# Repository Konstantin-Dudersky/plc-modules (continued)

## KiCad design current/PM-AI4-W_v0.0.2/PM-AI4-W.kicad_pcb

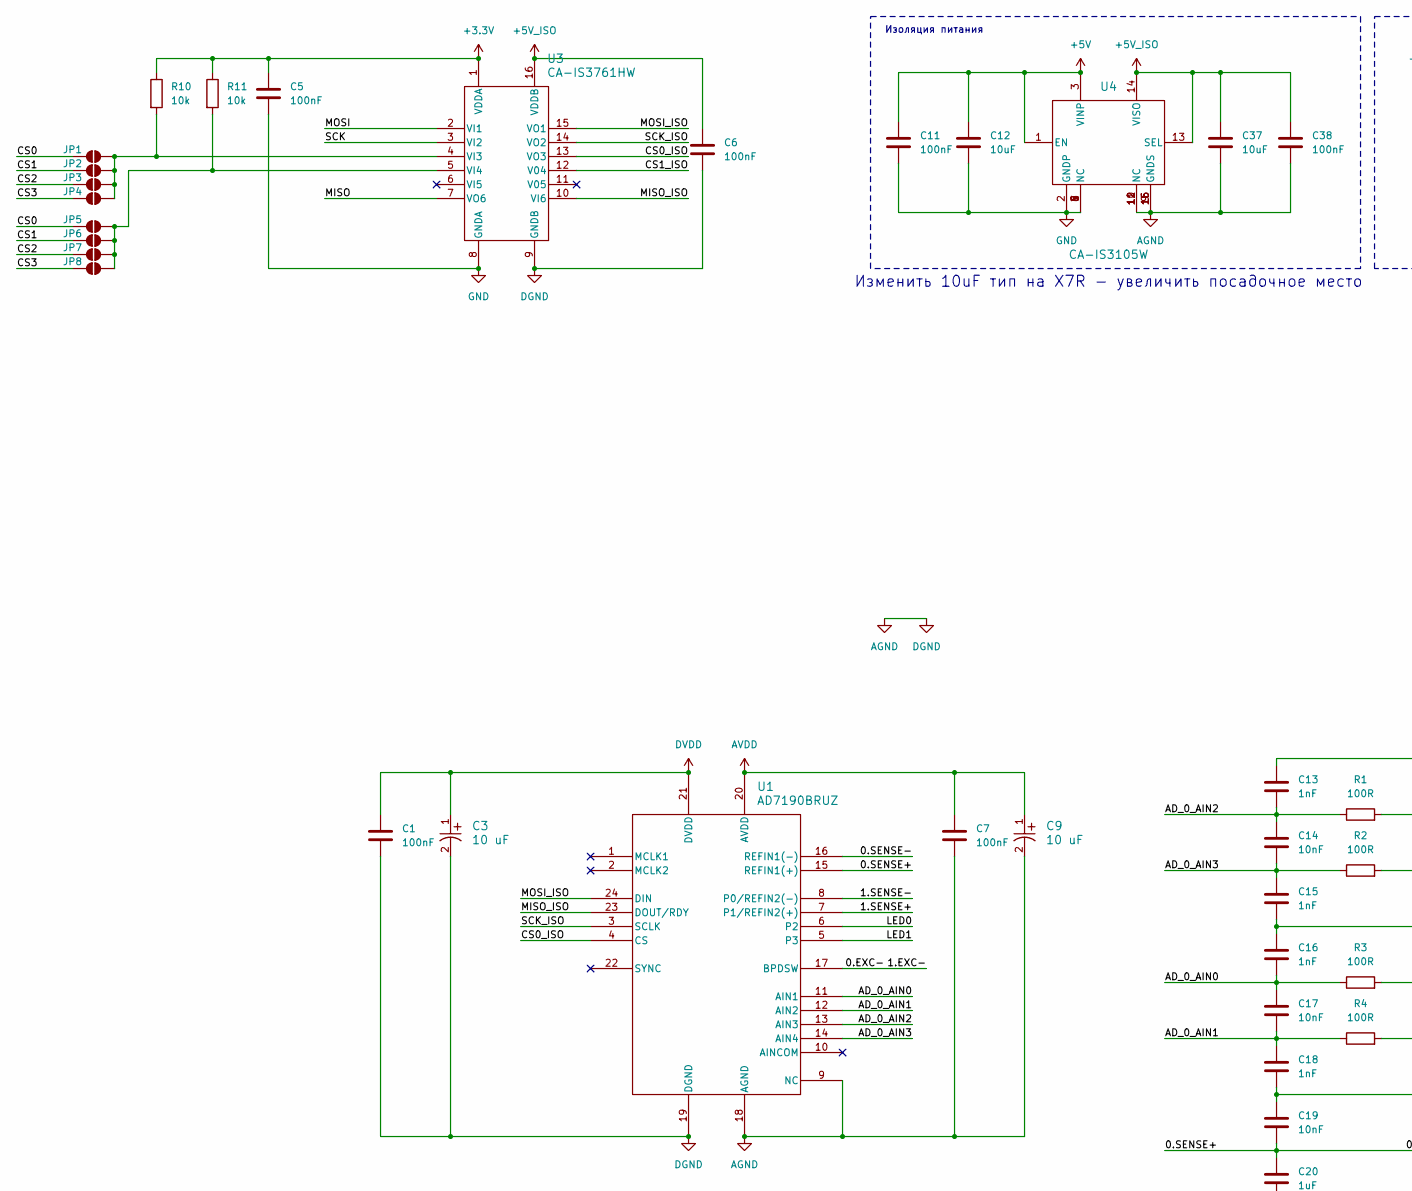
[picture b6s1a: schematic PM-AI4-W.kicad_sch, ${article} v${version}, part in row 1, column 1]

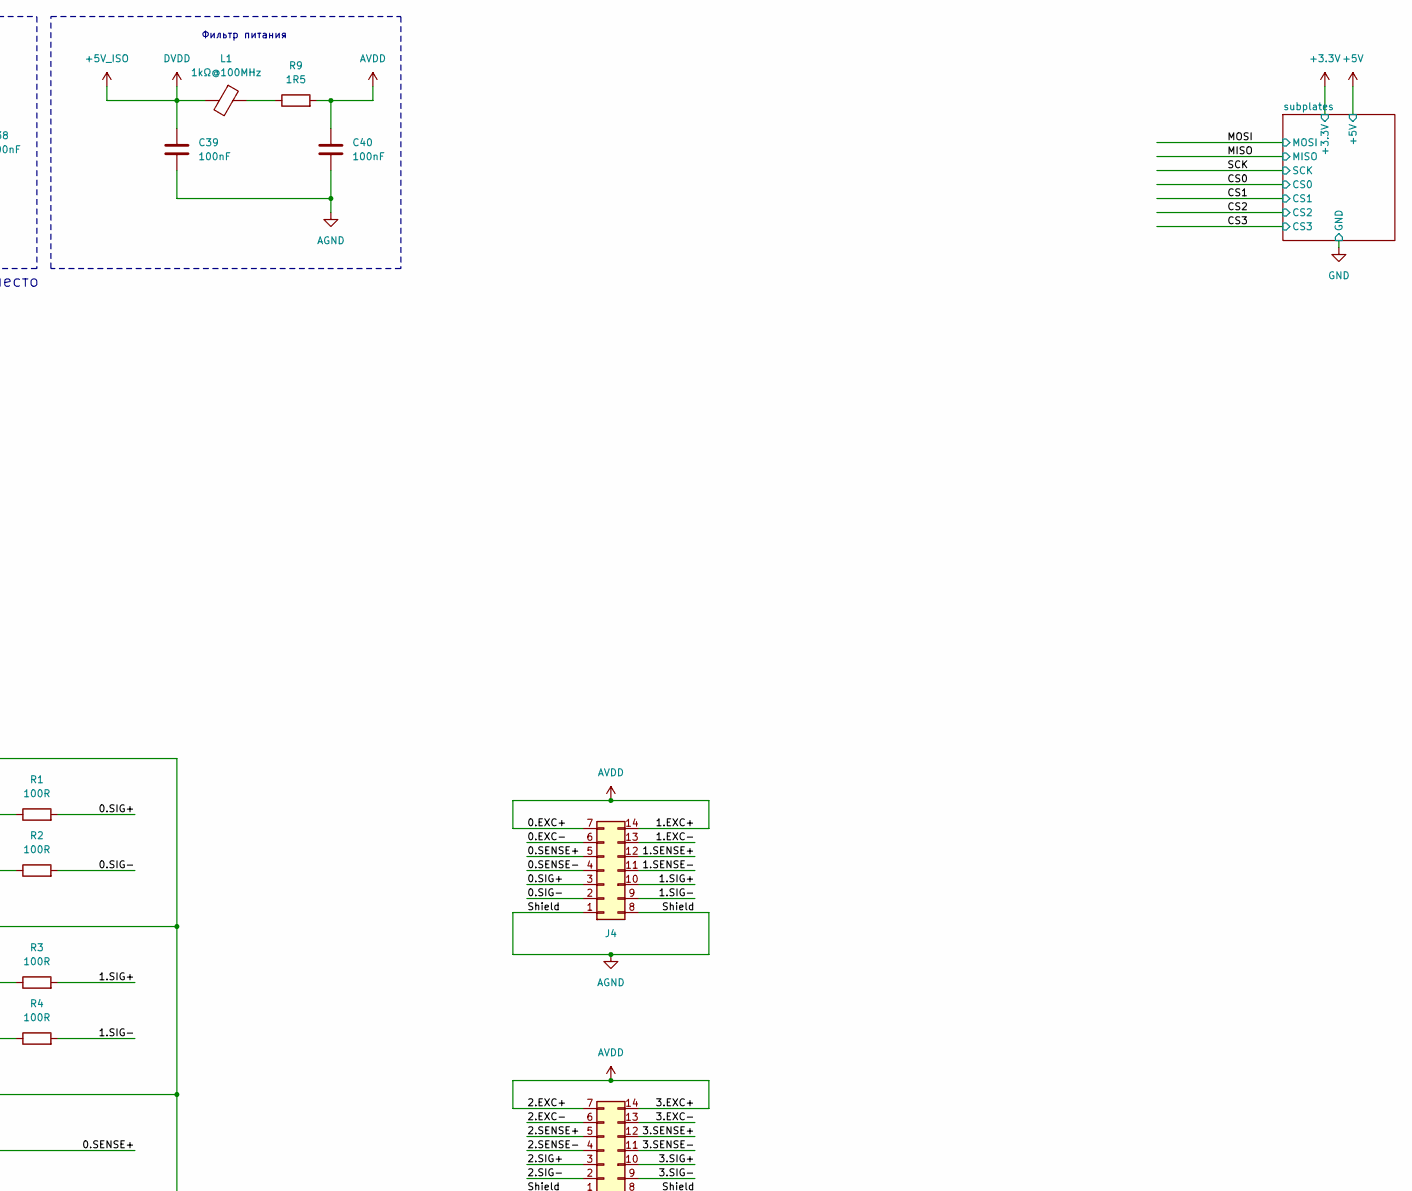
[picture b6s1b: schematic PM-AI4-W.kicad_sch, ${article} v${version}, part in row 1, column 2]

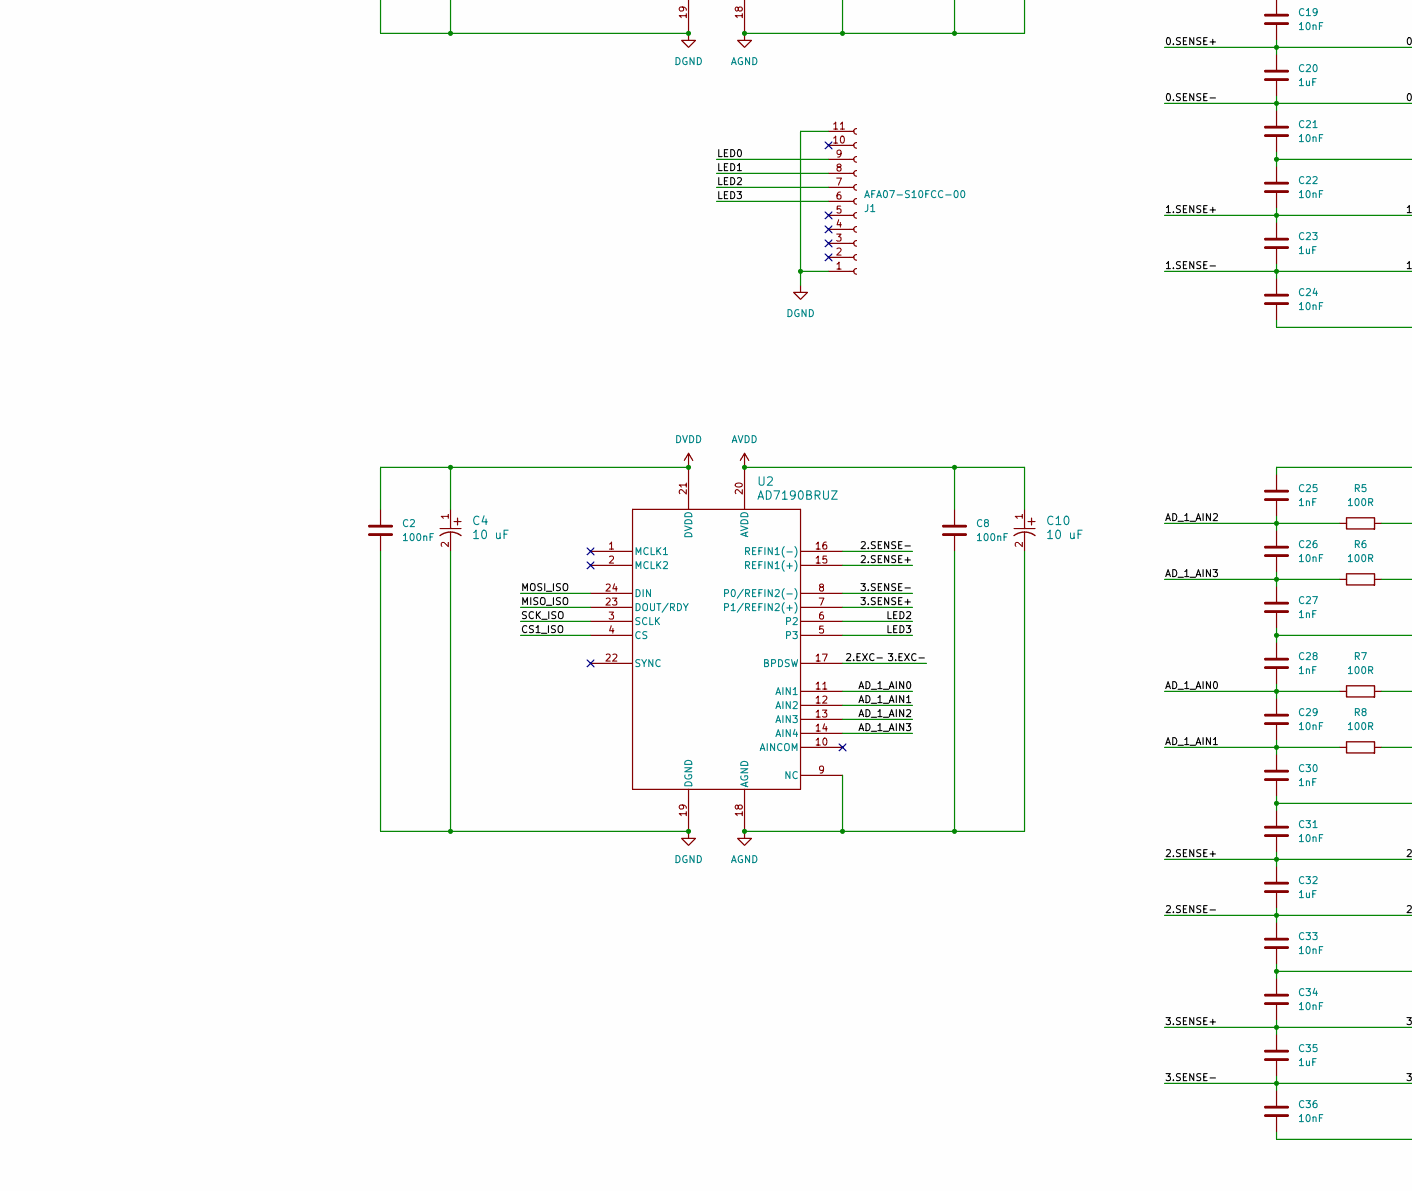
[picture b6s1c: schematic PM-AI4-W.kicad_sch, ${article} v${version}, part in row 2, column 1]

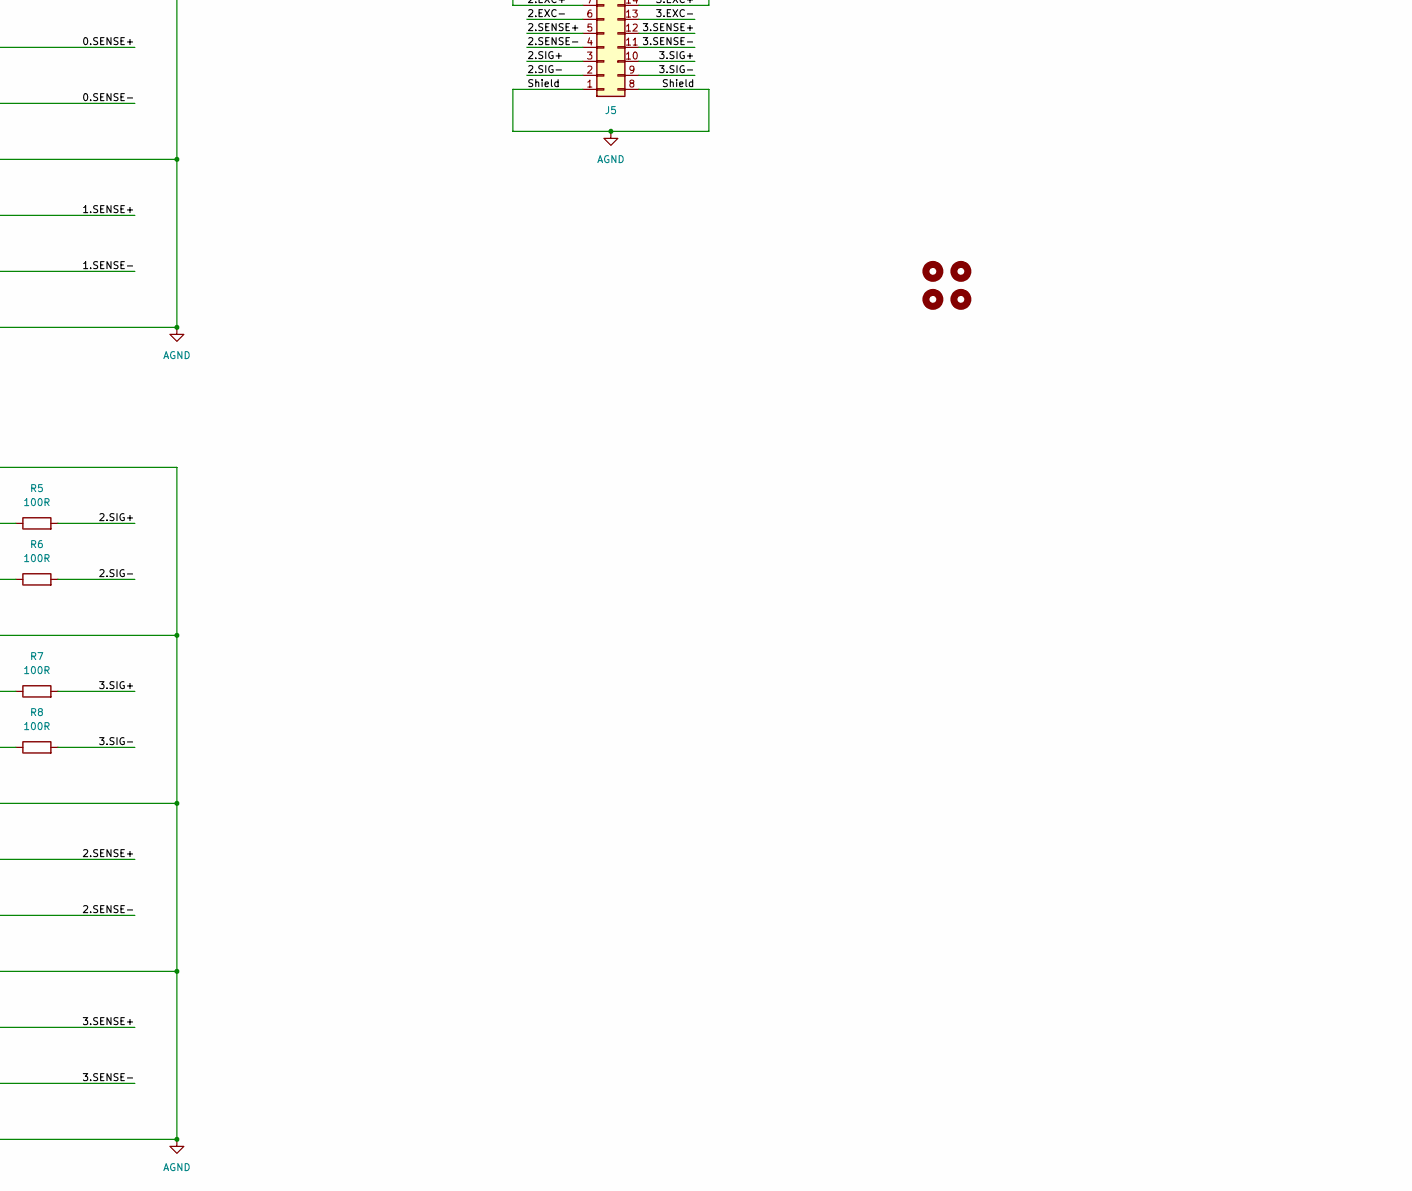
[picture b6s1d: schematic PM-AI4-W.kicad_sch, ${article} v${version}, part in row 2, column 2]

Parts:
C1, C2, C5, C6, C7, C8, C11, C38, C39, C40: 100nF; C_0603_1608Metric; part_ipn C_100nF_16V_0603_MLCC-X7R
C3, C4, C9, C10: 10 uF; TAJA_AVX-M; part_ipn TAJA106M016RNJ
C12, C37: 10uF; C_0603_1608Metric; part_ipn C_10uF_16V_0603_MLCC-X5R
C13, C15, C16, C18, C25, C27, C28, C30: 1nF; C_0603_1608Metric; part_ipn C_1nF_16V_0603_MLCC-X7R
C14, C17, C19, C21, C22, C24, C26, C29, C31, C33, C34, C36: 10nF; C_0603_1608Metric; part_ipn C_10nF_16V_0603_MLCC-X7R
C20, C23, C32, C35: 1uF; C_0603_1608Metric; part_ipn C_1uF_16V_0603_MLCC-X7R
H1, H2, H3, H4: MountingHole_M3
J1: AFA07-S10FCC-00; CONN10_AFA07-S10_JUS; part_ipn AFA07-S10FCC-00
J4, J5: 15EDGRHC-THR-3.5-14P; part_ipn 15EDGRHC-THR-3.5-14P
JP1, JP2, JP3, JP4, JP5, JP6, JP7, JP8: SolderJumper_2_Open; SolderJumper-2_P1.3mm_Open_RoundedPad1.0x1.5mm
L1: 1kΩ@100MHz; L_1206_3216Metric_Pad1.42x1.75mm_HandSolder; part_ipn FB_300mΩ_1kΩ@100MHz_1206
R1, R2, R3, R4, R5, R6, R7, R8: 100R; R_0603_1608Metric; part_ipn R_100R_0603_1%
R9: 1R5; R_0603_1608Metric; part_ipn R_1R5_0603_1%
R10, R11: 10k; R_0603_1608Metric; part_ipn R_10k_0603_1%
U1, U2: AD7190BRUZ; RU_24_ADI-M; part_ipn AD7190
U3: CA-IS3761HW; SOIC16-WBW_CLG-M; part_ipn CA-IS3761HW
U4: CA-IS3105W; SOIC16-WBW_CLG-M; part_ipn CA-IS3105W

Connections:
+3.3V: C5.1, R10.1, R11.1, U3.1 (VDDA); also elsewhere on the board
+5V: C11.1, C12.1, U4.1 (EN), U4.3 (VINP); also elsewhere on the board
+5V_ISO: C1.1, C2.1, C3.1, C4.1, C6.1, C37.1, C38.1, C39.1, L1.2, U1.21 (DVDD), U2.21 (DVDD), U3.16 (VDDB), U4.13 (SEL), U4.14 (VISO)
/0.EXC-: J4.6 (Pin_9), J4.13 (Pin_10), U1.17 (BPDSW)
/0.SENSE+: C19.2, C20.1, J4.5 (Pin_9), U1.15 (REFIN1(+))
/0.SENSE-: C20.2, C21.1, J4.4, U1.16 (REFIN1(-))
/0.SIG+: J4.3, R1.2
/0.SIG-: J4.2 (Pin_3), R2.2
/1.SENSE+: C22.2, C23.1, J4.12 (Pin_10), U1.7 (P1/REFIN2(+))
/1.SENSE-: C23.2, C24.1, J4.11 (Pin_8), U1.8 (P0/REFIN2(-))
/1.SIG+: J4.10 (Pin_6), R3.2
/1.SIG-: J4.9 (Pin_4), R4.2
/2.EXC-: J5.6 (Pin_9), J5.13 (Pin_10), U2.17 (BPDSW)
/2.SENSE+: C31.2, C32.1, J5.5 (Pin_9), U2.15 (REFIN1(+))
/2.SENSE-: C32.2, C33.1, J5.4, U2.16 (REFIN1(-))
/2.SIG+: J5.3, R5.2
/2.SIG-: J5.2 (Pin_3), R6.2
/3.SENSE+: C34.2, C35.1, J5.12 (Pin_10), U2.7 (P1/REFIN2(+))
/3.SENSE-: C35.2, C36.1, J5.11 (Pin_8), U2.8 (P0/REFIN2(-))
/3.SIG+: J5.10 (Pin_6), R7.2
/3.SIG-: J5.9 (Pin_4), R8.2
/AD_0_AIN0: C16.2, C17.1, R3.1, U1.11 (AIN1)
/AD_0_AIN1: C17.2, C18.1, R4.1, U1.12 (AIN2)
/AD_0_AIN2: C13.2, C14.1, R1.1, U1.13 (AIN3)
/AD_0_AIN3: C14.2, C15.1, R2.1, U1.14 (AIN4)
/AD_1_AIN0: C28.2, C29.1, R7.1, U2.11 (AIN1)
/AD_1_AIN1: C29.2, C30.1, R8.1, U2.12 (AIN2)
/AD_1_AIN2: C25.2, C26.1, R5.1, U2.13 (AIN3)
/AD_1_AIN3: C26.2, C27.1, R6.1, U2.14 (AIN4)
/CS0: JP1.1 (A), JP5.1 (A); also elsewhere on the board
/CS0_ISO: U1.4 (CS), U3.13 (VO3)
/CS1: JP2.1 (A), JP6.1 (A); also elsewhere on the board
/CS1_ISO: U2.4 (CS), U3.12 (V04)
/CS2: JP3.1 (A), JP7.1 (A); also elsewhere on the board
/CS3: JP4.1 (A), JP8.1 (A); also elsewhere on the board
/LED0: J1.9, U1.6 (P2)
/LED1: J1.8, U1.5 (P3)
/LED2: J1.7, U2.6 (P2)
/LED3: J1.6, U2.5 (P3)
/MISO: U3.7 (VO6); also elsewhere on the board
/MISO_ISO: U1.23 (DOUT/RDY), U2.23 (DOUT/RDY), U3.10 (VI6)
/MOSI: U3.2 (VI1); also elsewhere on the board
/MOSI_ISO: U1.24 (DIN), U2.24 (DIN), U3.15 (VO1)
/SCK: U3.3 (VI2); also elsewhere on the board
/SCK_ISO: U1.3 (SCLK), U2.3 (SCLK), U3.14 (VO2)
AGND: C1.2, C2.2, C3.2, C4.2, C6.2, C7.2, C8.2, C9.2, C10.2, C13.1, C15.2, C16.1, C18.2, C19.1, C21.2, C22.1, C24.2, C25.1, C27.2, C28.1, C30.2, C31.1, C33.2, C34.1, C36.2, C37.2, C38.2, C39.2, C40.2, J1.1, J1.11, J4.1, J4.8 (Pin_2), J5.1, J5.8 (Pin_2), U1.9 (NC), U1.18 (AGND), U1.19 (DGND), U2.9 (NC), U2.18 (AGND), U2.19 (DGND), U3.9 (GNDB), U4.9 (GNDS), U4.10 (NC), U4.11 (NC), U4.12 (NC), U4.15 (GNDS), U4.16 (GNDS)
AVDD: C7.1, C8.1, C9.1, C10.1, C40.1, J4.7 (Pin_9), J4.14 (Pin_10), J5.7 (Pin_9), J5.14 (Pin_10), R9.2, U1.20 (AVDD), U2.20 (AVDD)
GND: C5.2, C11.2, C12.2, U3.8 (GNDA), U4.2 (GNDP), U4.4 (NC), U4.5 (NC), U4.6 (NC), U4.7 (NC), U4.8 (NC); also elsewhere on the board
unnamed: JP1.2 (B), JP2.2 (B), JP3.2 (B), JP4.2 (B), R10.2, U3.4 (VI3)
unnamed: JP5.2 (B), JP6.2 (B), JP7.2 (B), JP8.2 (B), R11.2, U3.5 (VI4)
unnamed: L1.1, R9.1

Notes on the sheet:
Изменить 10uF тип на X7R - увеличить посадочное место
Фильтр питания
Изоляция питания

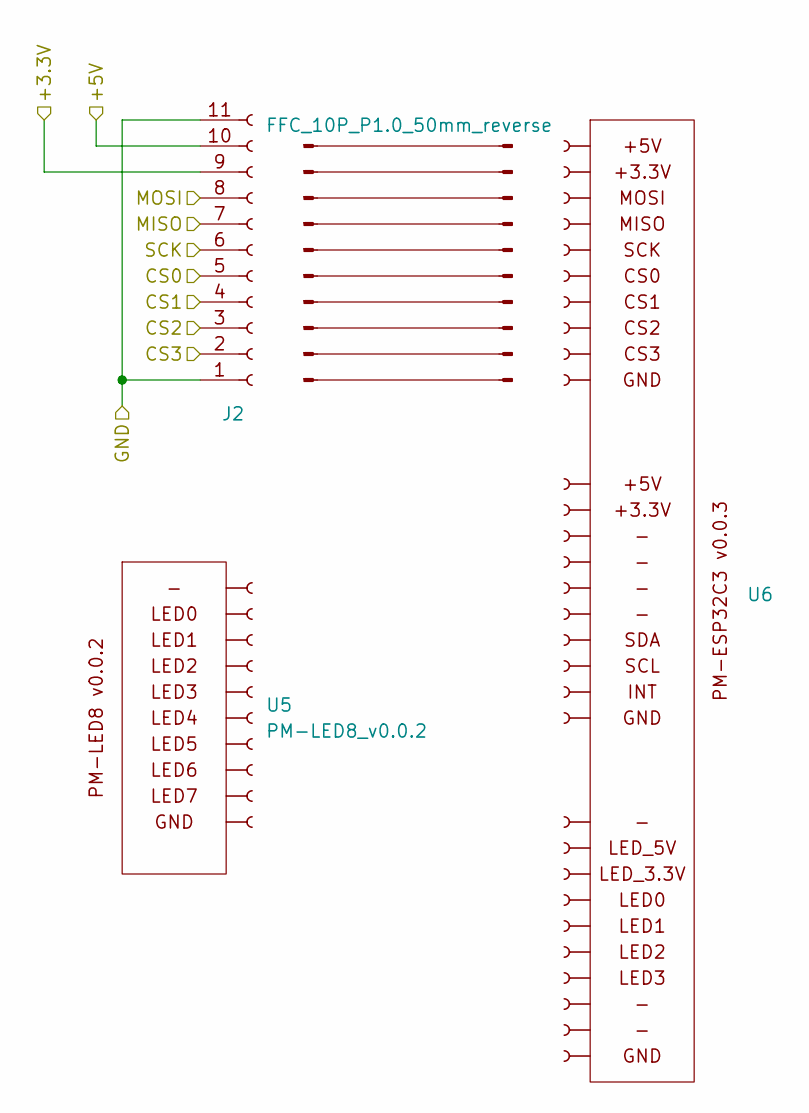
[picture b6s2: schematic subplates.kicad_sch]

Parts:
J2: AFA07-S10FCC-00; CONN10_AFA07-S10_JUS; part_ipn AFA07-S10FCC-00
J3: FFC_10P_P1.0_50mm_reverse; part_ipn FFC_10P_P1.0_50mm_reverse
U5: PM-LED8_v0.0.2; PM-LED_v0.0.2; part_ipn PM-LED8_v0.0.2
U6: PM-ESP32C3_v0.0.4; part_ipn PM-ESP32C3_v0.0.4

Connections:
+3.3V: J2.9; also elsewhere on the board
+5V: J2.10; also elsewhere on the board
/CS0: J2.5; also elsewhere on the board
/CS1: J2.4; also elsewhere on the board
/CS2: J2.3; also elsewhere on the board
/CS3: J2.2; also elsewhere on the board
/MISO: J2.7; also elsewhere on the board
/MOSI: J2.8; also elsewhere on the board
/SCK: J2.6; also elsewhere on the board
GND: J2.1, J2.11; also elsewhere on the board

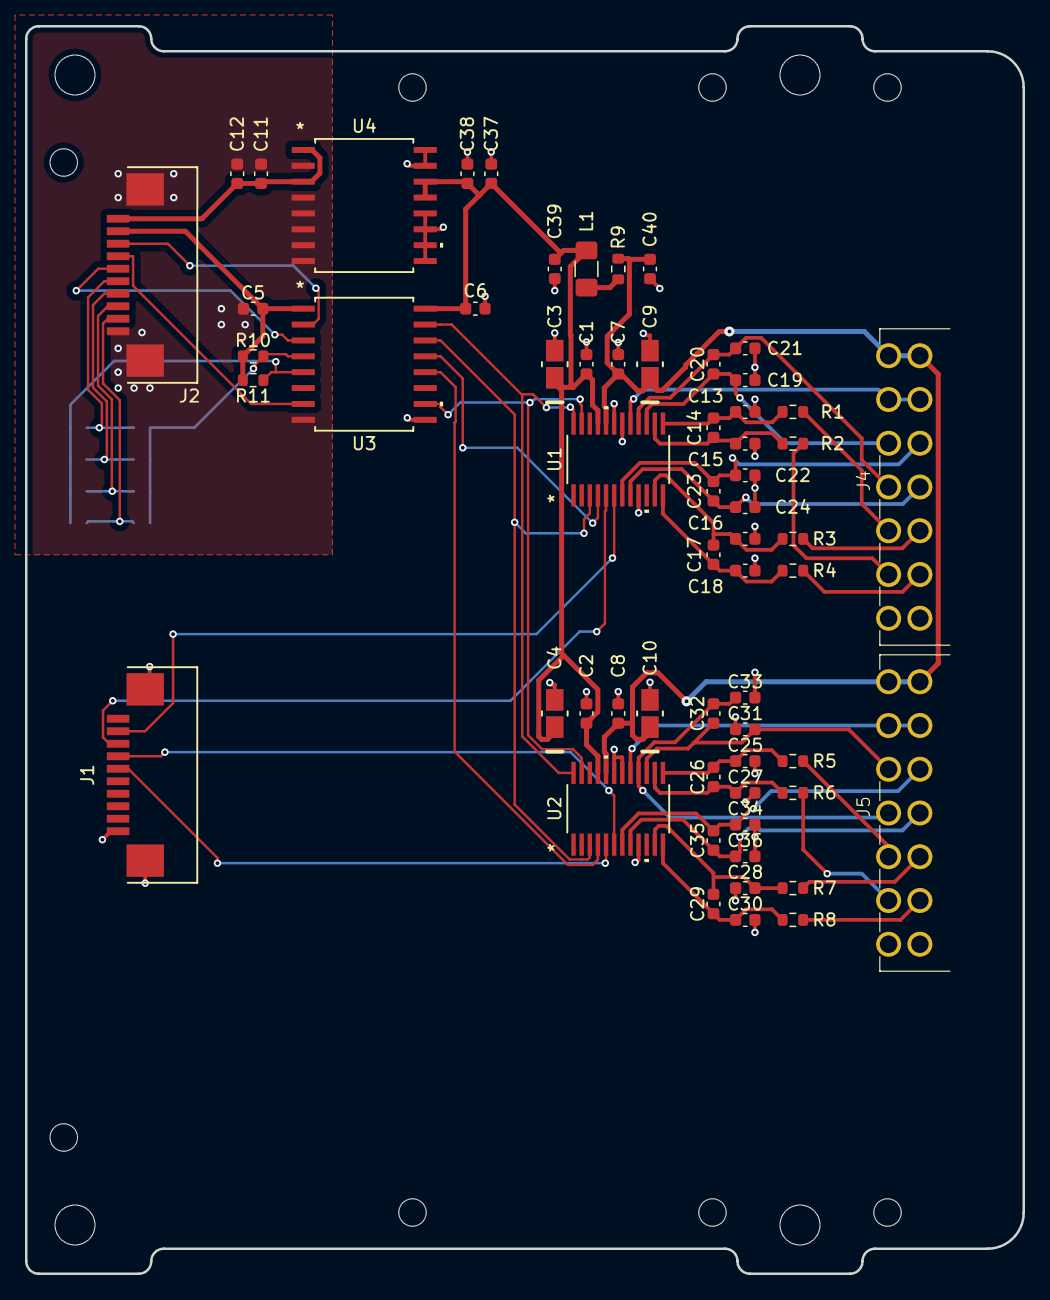
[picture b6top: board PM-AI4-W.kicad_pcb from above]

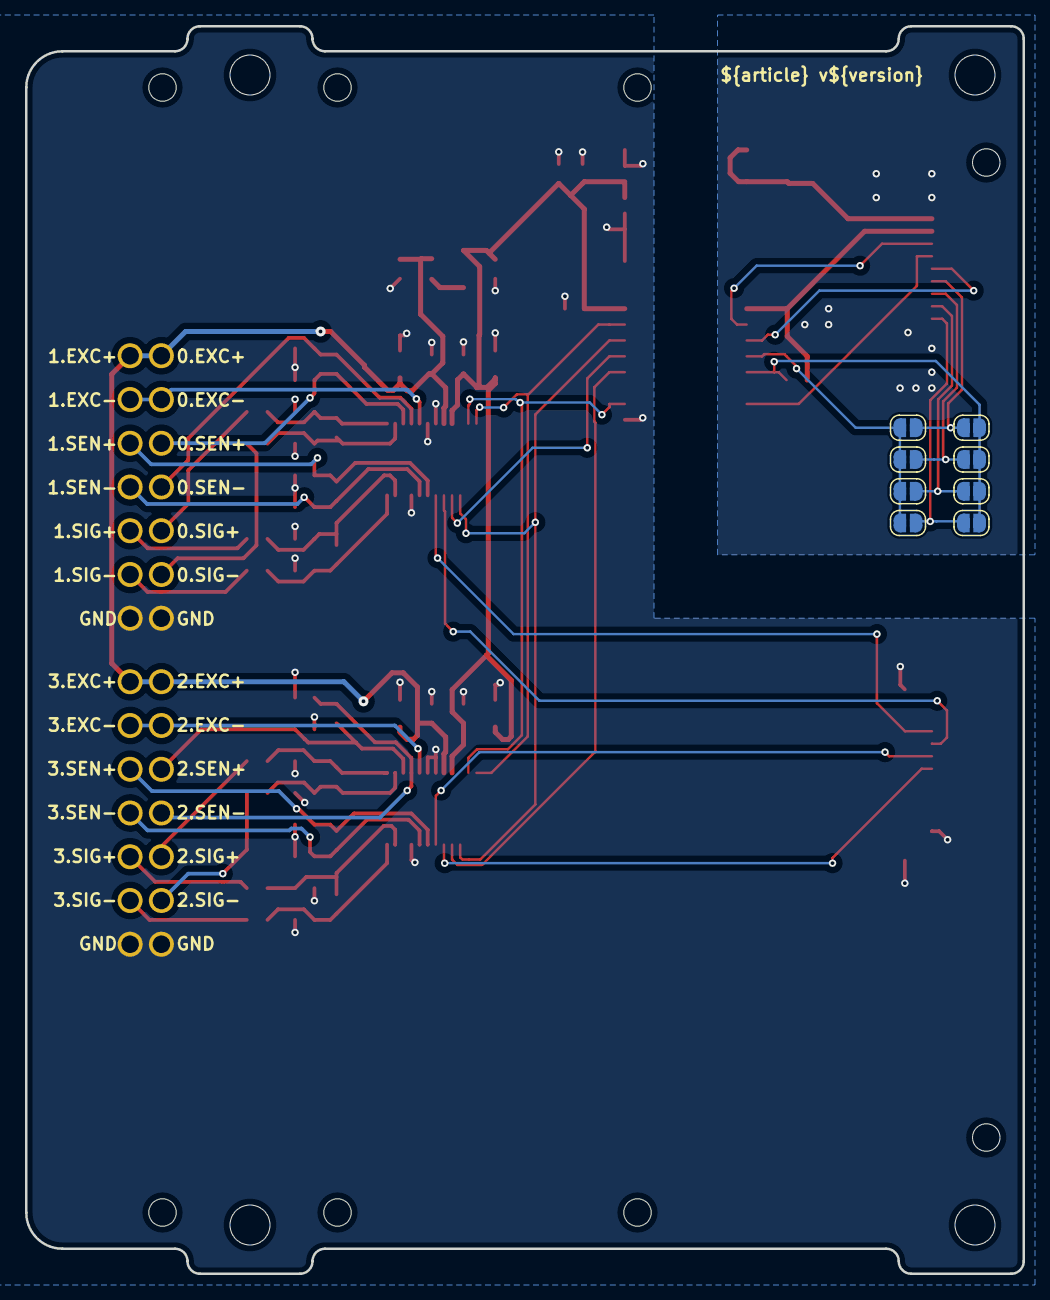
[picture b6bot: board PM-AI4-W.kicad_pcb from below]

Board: 2 copper layers, 79.8 x 99.8 mm, 74 parts (8 on the bottom side), 51 nets.

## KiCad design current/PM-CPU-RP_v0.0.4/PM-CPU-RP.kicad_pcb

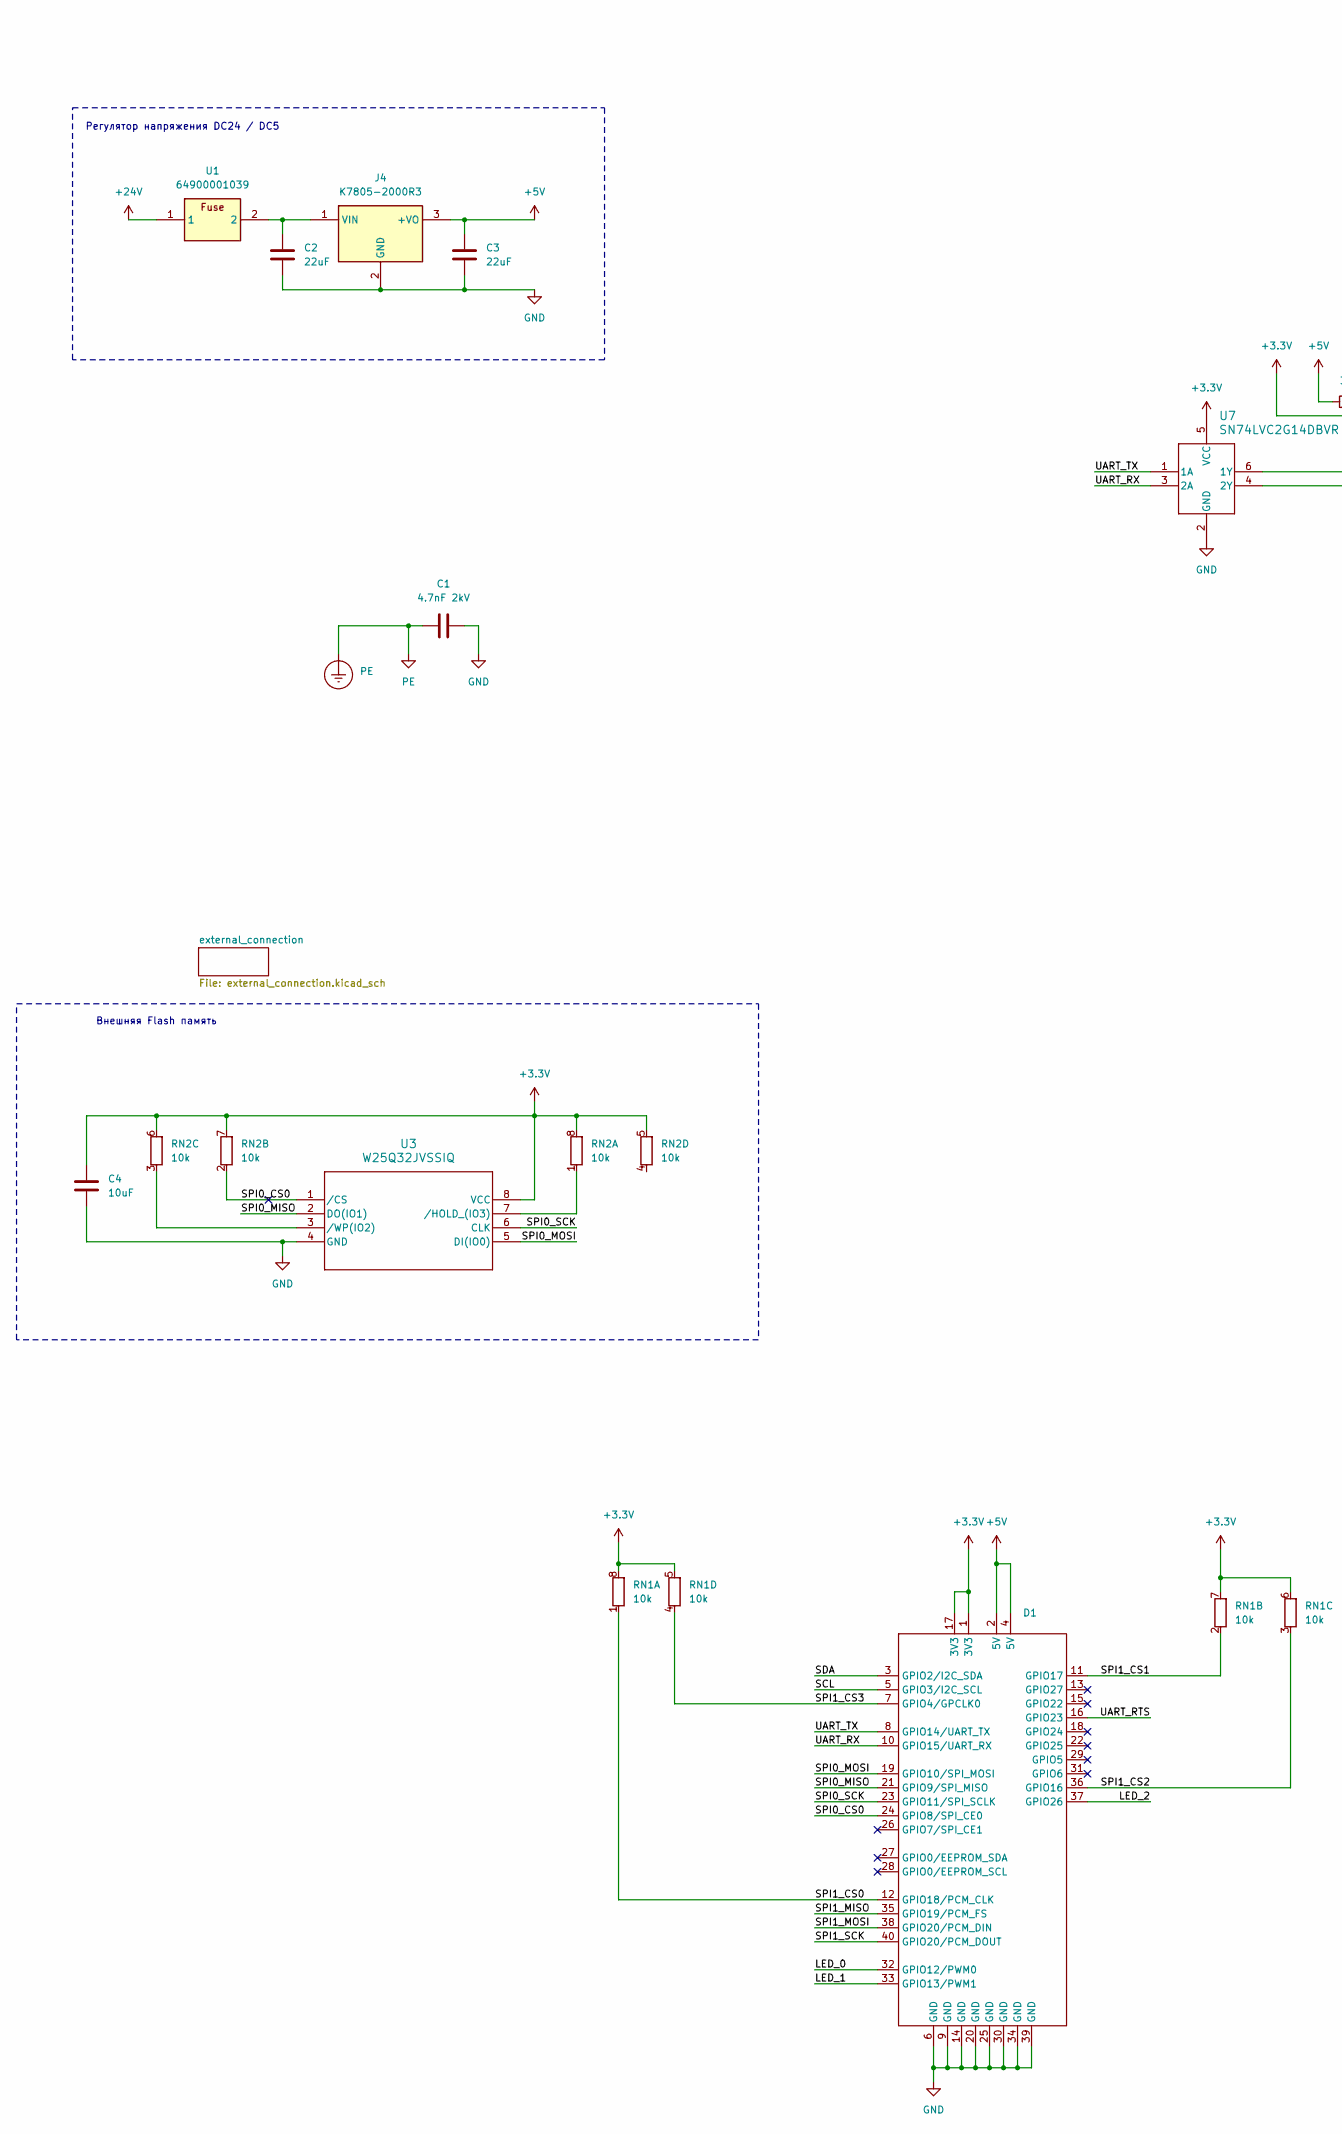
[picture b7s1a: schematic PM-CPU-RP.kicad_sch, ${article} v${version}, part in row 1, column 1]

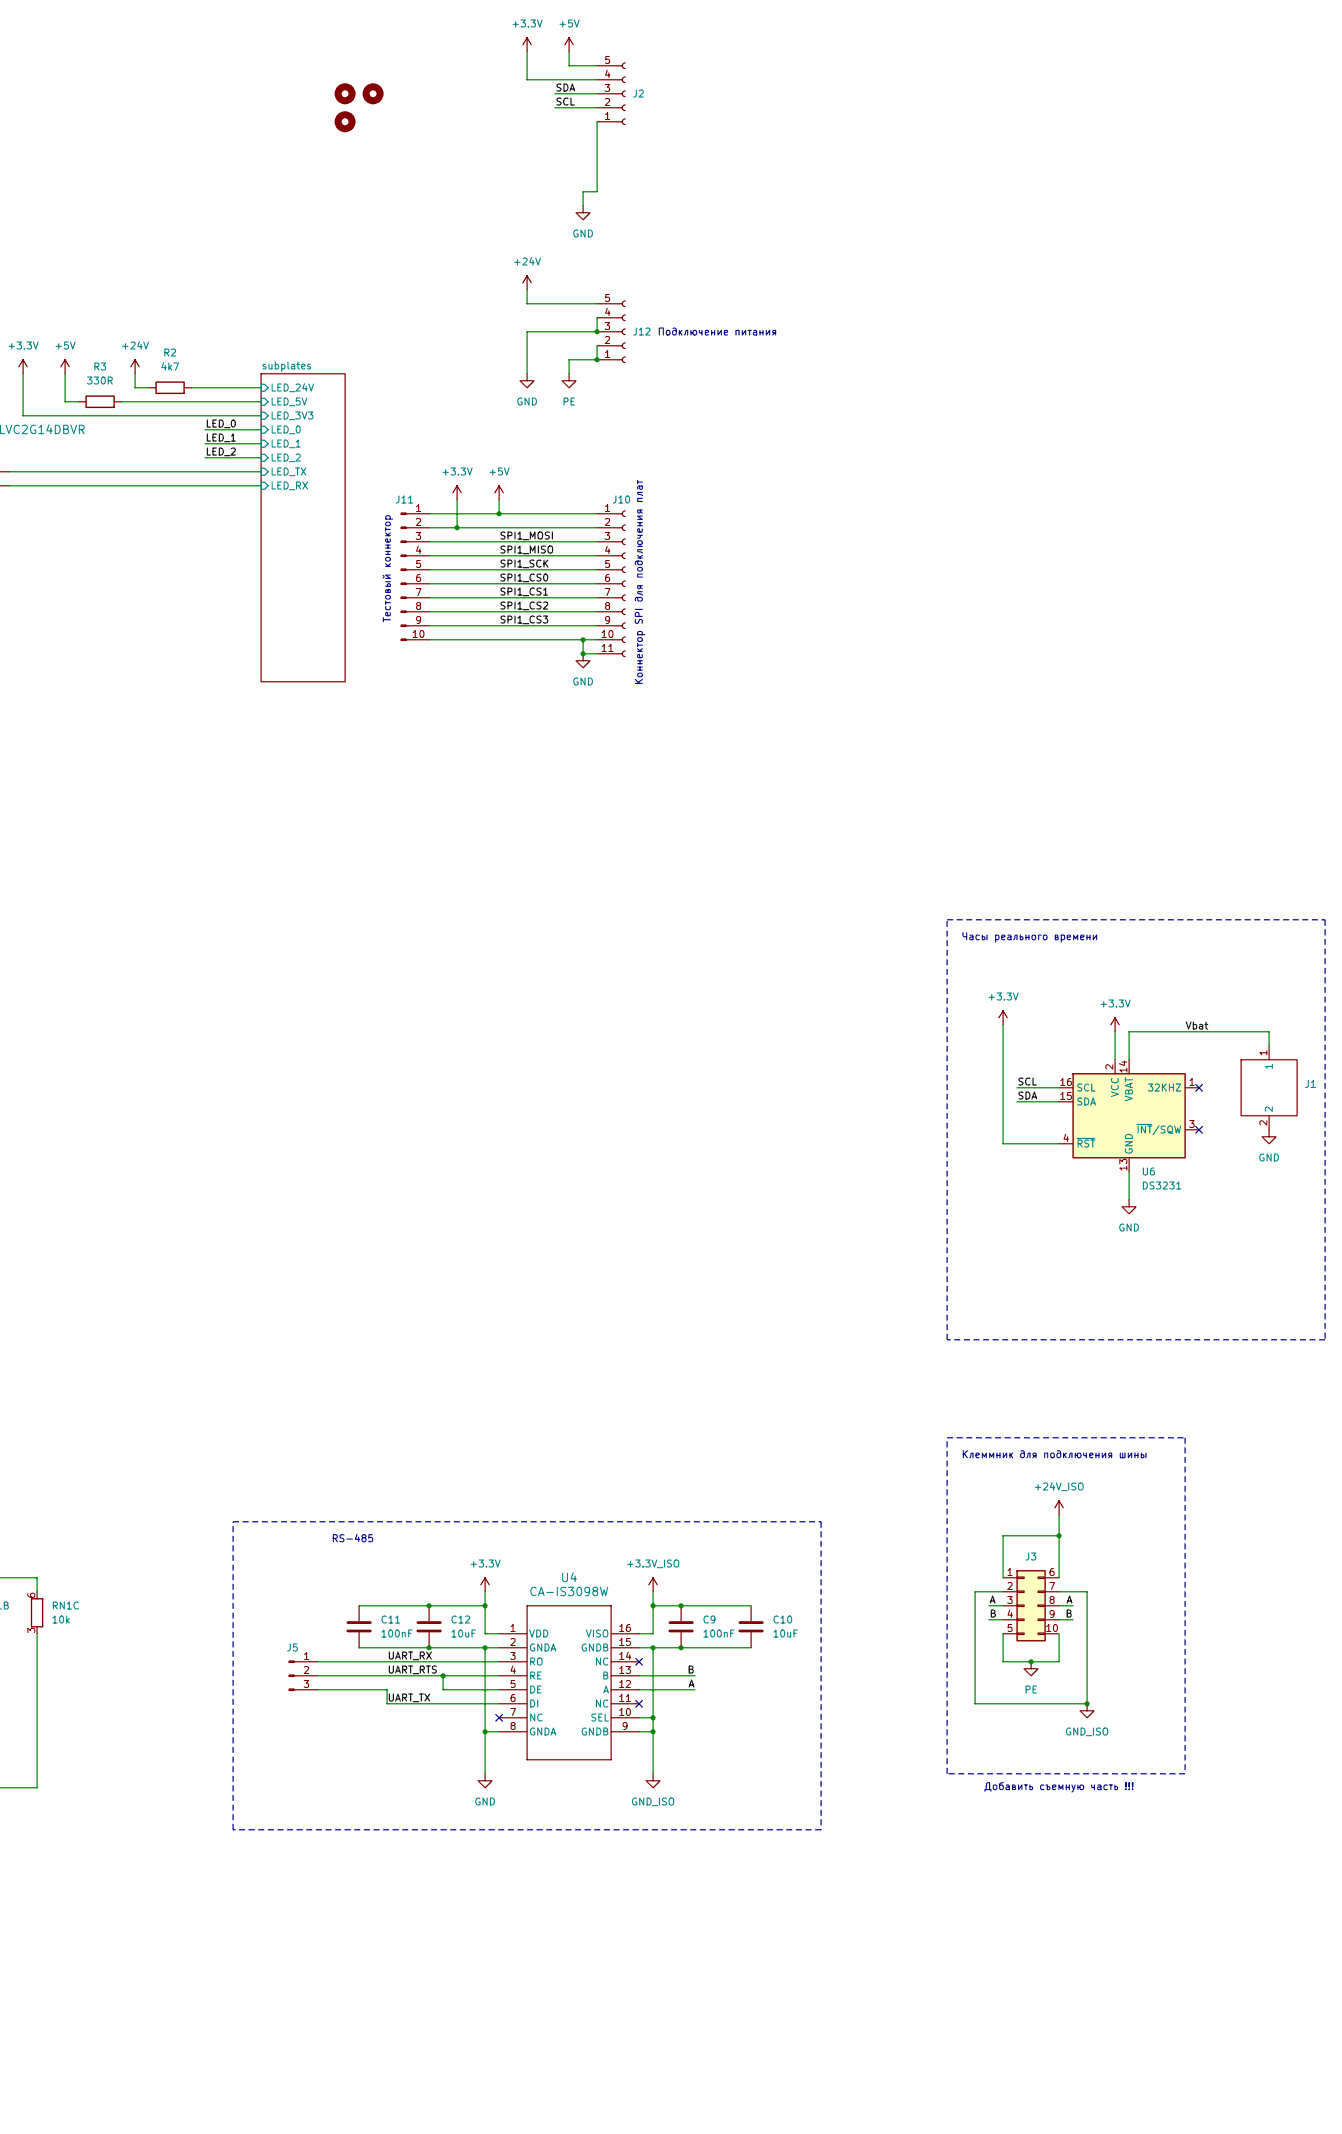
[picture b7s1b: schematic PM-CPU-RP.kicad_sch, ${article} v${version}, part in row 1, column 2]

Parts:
C1: 4.7nF 2kV; C_1812_4532Metric_Pad1.57x3.40mm_HandSolder; part_ipn C_4.7nF_2kV_1812
C2, C3: 22uF; C_2220_5750Metric; part_ipn C_22uF_50V_2220
C4, C10, C12: 10uF; C_0805_2012Metric; part_ipn C_10uF_16V_0805_MLCC-X5R
C9, C11: 100nF; C_0603_1608Metric; part_ipn C_100nF_16V_0603_MLCC-X7R
D1: RaspberryPi
H1, H2, H3: MountingHole_M3
J1: BS-12-A1AJ002-F; part_ipn BS-12-A1AJ002-F
J2, J12: 15EDGRC-3.5-05P; part_ipn 15EDGRC-3.5-05P
J3: 15EDGRHC-THR-3.5-10P; part_ipn 15EDGRHC-THR-3.5-10P
J4: K7805-2000R3; Manufacturer_Part_Number K7805-2000R3
J5: Conn_01x03_Pin; PinHeader_1x03_P1.00mm_Vertical
J10: AFA07-S10FCC-00; CONN10_AFA07-S10_JUS; part_ipn AFA07-S10FCC-00
J11: Conn_01x10_Pin; PinHeader_1x10_P1.00mm_Vertical
PE1: PE
R2: 4k7; R_0603_1608Metric; part_ipn R_4k7_0603_1%
R3: 330R; R_0603_1608Metric; part_ipn R_330R_0603_1%
RN1, RN2: 10k; R_Array_Convex_4x0603; part_ipn R_10k_0603x4_1%
U1: 64900001039; Fuseholder; Manufacturer_Part_Number 64900001039; Mouser Part Number 576-64900001039
U3: W25Q32JVSSIQ; SOIC-8_5P28X5P28_WIN-M
U4: CA-IS3098W; SOIC16-WBW_CLG; part_ipn CA-IS3098W
U6: DS3231; SOIC-16W_7.5x10.3mm_P1.27mm; part_ipn DS3231SN
U7: SN74LVC2G14DBVR; DBV6-M

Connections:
+3.3V: C4.1, C11.1, C12.1, D1.1 (3V3), D1.17 (3V3), J2.4, J10.2, J11.2, RN1.5 (R4.2), RN1.6 (R3.2), RN1.7 (R2.2), RN1.8 (R1.2), RN2.5 (R4.2), RN2.6 (R3.2), RN2.7 (R2.2), RN2.8 (R1.2), U3.8 (VCC), U4.1 (VDD), U6.2 (VCC), U6.4 (~RST), U7.5 (VCC); also elsewhere on the board
+3.3V_ISO: C9.1, C10.1, U4.16 (VISO)
+5V: C3.1, D1.2 (5V), D1.4 (5V), J2.5, J4.3 (+VO), J10.1, J11.1, R3.1
+24V: J12.5, R2.1, U1.1
+24V_ISO: J3.1, J3.6 (Pin_2)
/A: J3.3, J3.8 (Pin_6), U4.12 (A)
/B: J3.4, J3.9 (Pin_8), U4.13 (B)
/LED_0: D1.32 (GPIO12/PWM0); also elsewhere on the board
/LED_1: D1.33 (GPIO13/PWM1); also elsewhere on the board
/LED_2: D1.37 (GPIO26); also elsewhere on the board
/SCL: D1.5 (GPIO3/I2C_SCL), J2.2, U6.16 (SCL)
/SDA: D1.3 (GPIO2/I2C_SDA), J2.3, U6.15 (SDA)
/SPI0_CS0: D1.24 (GPIO8/SPI_CE0), RN2.2 (R2.1), U3.1 (/CS)
/SPI0_MISO: D1.21 (GPIO9/SPI_MISO), U3.2 (DO(IO1))
/SPI0_MOSI: D1.19 (GPIO10/SPI_MOSI), U3.5 (DI(IO0))
/SPI0_SCK: D1.23 (GPIO11/SPI_SCLK), U3.6 (CLK)
/SPI1_CS0: D1.12 (GPIO18/PCM_CLK), J10.6, J11.6, RN1.1 (R1.1)
/SPI1_CS1: D1.11 (GPIO17), J10.7, J11.7, RN1.2 (R2.1)
/SPI1_CS2: D1.36 (GPIO16), J10.8, J11.8, RN1.3 (R3.1)
/SPI1_CS3: D1.7 (GPIO4/GPCLK0), J10.9, J11.9, RN1.4 (R4.1)
/SPI1_MISO: D1.35 (GPIO19/PCM_FS), J10.4, J11.4
/SPI1_MOSI: D1.38 (GPIO20/PCM_DIN), J10.3, J11.3
/SPI1_SCK: D1.40 (GPIO20/PCM_DOUT), J10.5, J11.5
/UART_RTS: D1.16 (GPIO23), J5.2, U4.4 (RE), U4.5 (DE)
/UART_RX: D1.10 (GPIO15/UART_RX), J5.1, U4.3 (RO), U7.3 (2A)
/UART_TX: D1.8 (GPIO14/UART_TX), J5.3, U4.6 (DI), U7.1 (1A)
/Vbat: J1.1, U6.14 (VBAT)
/subplates/LED_5V: R3.2; also elsewhere on the board
/subplates/LED_24V: R2.2; also elsewhere on the board
/subplates/LED_RX: U7.4 (2Y); also elsewhere on the board
/subplates/LED_TX: U7.6 (1Y); also elsewhere on the board
GND: C1.2, C2.2, C3.2, C4.2, C11.2, C12.2, D1.6 (GND), D1.9 (GND), D1.14 (GND), D1.20 (GND), D1.25 (GND), D1.30 (GND), D1.34 (GND), D1.39 (GND), J1.2, J2.1, J4.2 (GND), J10.10, J10.11, J11.10, J12.3, J12.4, U3.4 (GND), U4.2 (GNDA), U4.8 (GNDA), U6.5 (GND), U6.6 (GND), U6.7 (GND), U6.8 (GND), U6.9 (GND), U6.10 (GND), U6.11 (GND), U6.12 (GND), U6.13 (GND), U7.2 (GND)
GND_ISO: C9.2, C10.2, J3.2 (Pin_3), J3.7 (Pin_4), U4.9 (GNDB), U4.10 (SEL), U4.15 (GNDB)
unnamed: C2.1, J4.1 (VIN), U1.2
unnamed: RN2.1 (R1.1), U3.7 (/HOLD_(IO3))
unnamed: RN2.3 (R3.1), U3.3 (/WP(IO2))
PE: C1.1, J3.5 (Pin_9), J3.10, J12.1, J12.2, PE1.1

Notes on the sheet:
Клеммник для подключения шины
RS-485
Тестовый коннектор
Внешняя Flash память
Подключение питания
Добавить съемную часть !!!
Коннектор SPI для подключения плат
Часы реального времени
Регулятор напряжения DC24 / DC5

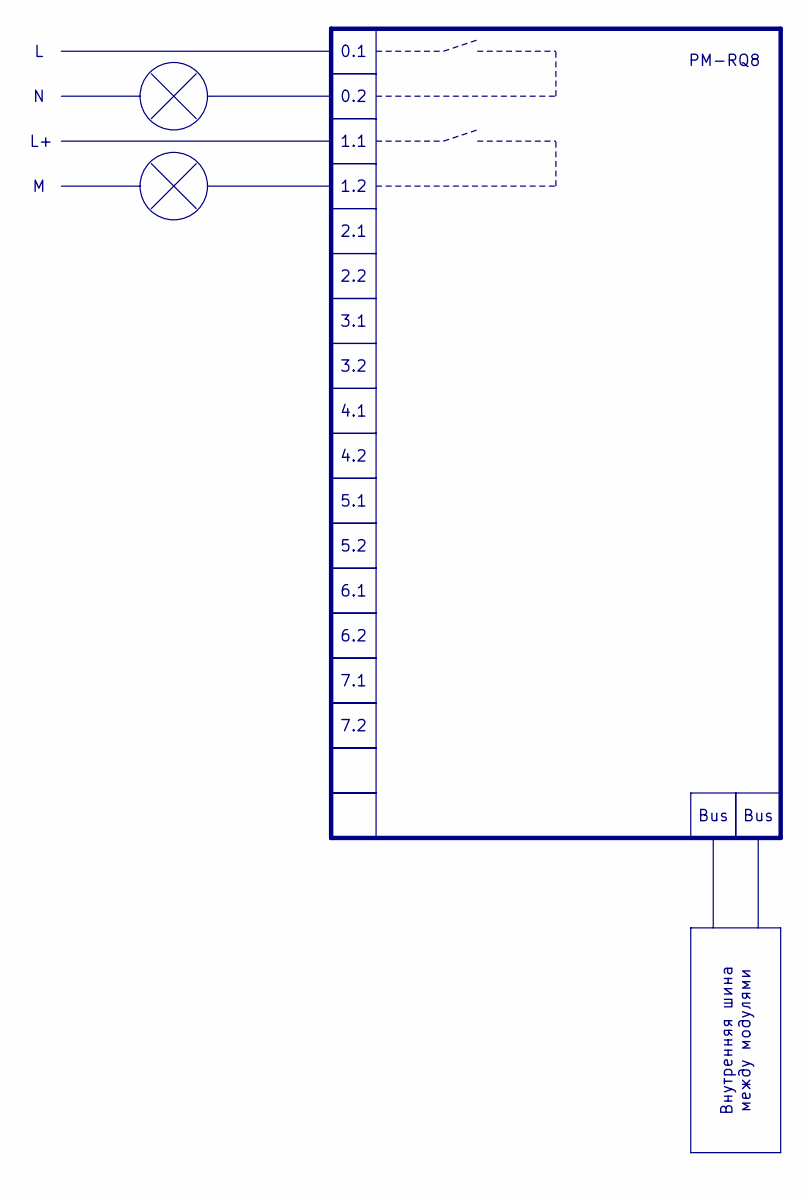
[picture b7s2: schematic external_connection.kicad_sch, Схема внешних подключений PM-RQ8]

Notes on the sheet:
2.2
Bus
5.1
1.2
2.1
6.2
4.1
0.2
5.2
4.2
0.1
3.1
Внутренняя шина между модулями
7.2
7.1
1.1
6.1
3.2
PM-RQ8
